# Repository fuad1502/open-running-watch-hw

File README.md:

# *open-running-watch* (Hardware Repository)

An Open Source GPS Running Watch. 🏃⌚

> Note: This is the hardware repository. The firmware repository isn't available yet.

## Motivation

Running is my hobby, and ask anyone who has taken their running hobby seriously and they'll tell you having a GPS running watch is a must. Throughout my time using one, I sometimes encounter issues and thought to myself, "Why does it happen?", "I wish I had access to the raw data", "Why is the latest model way more expensive for just an additional sensor or software feature?", "I wish I could tune my watch to the way I wanted it, for longer battery life or better user experience", etc.

My wishes can only be fulfilled if there is a GPS running watch out there that is open sourced. Free for everyone to add their own software features, experiment with different algorithms, different chips, and produce their own customized hardware version, designed to exactly what they want.

I know what you're thinking. Who in the world would want that? Firstly, they have to be a runner, secondly, they have to be either a hardware geek and / or a software geek. Well, I am both! So I want it! And that's a good enough reason for me to build this 😁

However, in truth, that's not actually my main motivation for initiating this project. **My main motivation is I wanted to try out [Zephyr Project](https://www.zephyrproject.org/) on a complex embedded system.**

## Main components

- Main controller (STM32L475RGT6)
- Display (Azumo 12616: Sharp LS018B7DH02 Memory in Pixel Display)
- GPS receiver (TESEO-LIV3F)
- BLE wireless network coprocessor (BLUENRG-232N)
- Barometric pressure sensor (ICP-10100)
- Accelerometer (LIS2DE12TR)
- PPG Sensor (SFH7072)
- NAND Flash Memory (W25N512GVEIG)
- Fuel gauge & charge controller
- Audio indicator
- 5 user input buttons
- Current sense amplifiers for power usage monitoring in the development phase

## PCB Stackup

I use [JLCPCB JLC04161H-7628](https://jlcpcb.com/impedance) 4 layer stackup with the following signal assignments:

```
=========================
= (F.Cu) SIGNAL         =
=========================
PREPREG
=========================
= (In1.Cu) GROUND PLANE =
=========================
CORE
=========================
= (In2.Cu) POWER PLANE  =
=========================
PREPREG
=========================
= (B.Cu) SIGNAL         =
=========================
```

## Fabrication Files

You can download the released fabrication files tarball in the [Release](https://github.com/fuad1502/open-running-watch-hw/releases) tab. It contains:
- Schematic PDF.
- Top, bottom, and power plane PCB drawing.
- Gerbers.
- Bill of Materials.

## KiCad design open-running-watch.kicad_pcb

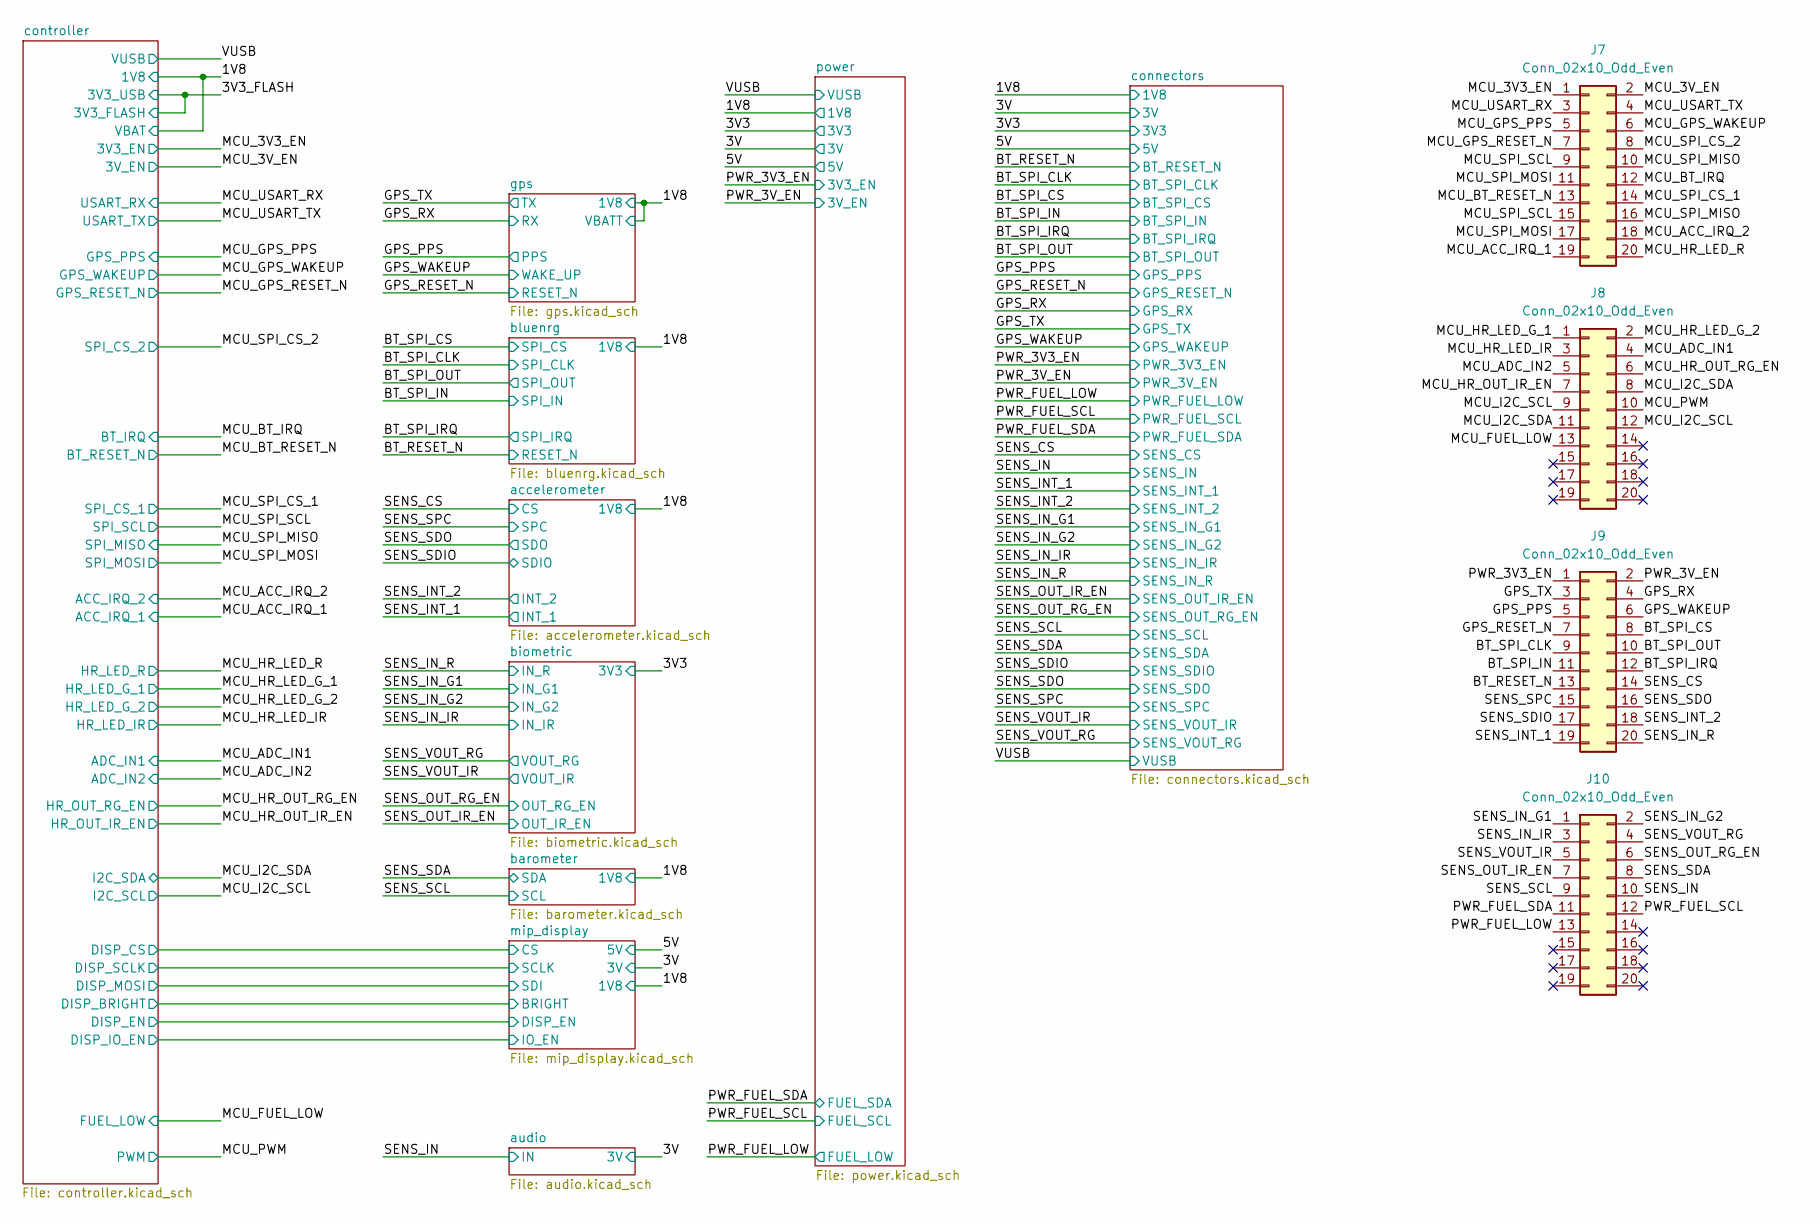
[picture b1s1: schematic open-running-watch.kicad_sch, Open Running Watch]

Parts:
J7, J8, J9, J10: Conn_02x10_Odd_Even; PinHeader_2x10_P2.54mm_Vertical_SMD

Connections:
/BT_RESET_N: J9.13; also elsewhere on the board
/BT_SPI_CLK: J9.9; also elsewhere on the board
/BT_SPI_CS: J9.8; also elsewhere on the board
/BT_SPI_IN: J9.11; also elsewhere on the board
/BT_SPI_IRQ: J9.12; also elsewhere on the board
/BT_SPI_OUT: J9.10; also elsewhere on the board
/GPS_PPS: J9.5; also elsewhere on the board
/GPS_RESET_N: J9.7; also elsewhere on the board
/GPS_RX: J9.4; also elsewhere on the board
/GPS_TX: J9.3; also elsewhere on the board
/GPS_WAKEUP: J9.6; also elsewhere on the board
/MCU_3V3_EN: J7.1
/MCU_3V_EN: J7.2
/MCU_ACC_IRQ_1: J7.19; also elsewhere on the board
/MCU_ACC_IRQ_2: J7.18; also elsewhere on the board
/MCU_ADC_IN1: J8.4; also elsewhere on the board
/MCU_ADC_IN2: J8.5; also elsewhere on the board
/MCU_BT_IRQ: J7.12; also elsewhere on the board
/MCU_BT_RESET_N: J7.13; also elsewhere on the board
/MCU_FUEL_LOW: J8.13
/MCU_GPS_PPS: J7.5
/MCU_GPS_RESET_N: J7.7; also elsewhere on the board
/MCU_GPS_WAKEUP: J7.6; also elsewhere on the board
/MCU_HR_LED_G_1: J8.1; also elsewhere on the board
/MCU_HR_LED_G_2: J8.2; also elsewhere on the board
/MCU_HR_LED_IR: J8.3; also elsewhere on the board
/MCU_HR_LED_R: J7.20; also elsewhere on the board
/MCU_HR_OUT_IR_EN: J8.6, J8.7; also elsewhere on the board
/MCU_I2C_SCL: J8.9, J8.12; also elsewhere on the board
/MCU_I2C_SDA: J8.8, J8.11; also elsewhere on the board
/MCU_PWM: J8.10; also elsewhere on the board
/MCU_SPI_CS_1: J7.14; also elsewhere on the board
/MCU_SPI_CS_2: J7.8; also elsewhere on the board
/MCU_SPI_MISO: J7.10, J7.16; also elsewhere on the board
/MCU_SPI_MOSI: J7.11, J7.17; also elsewhere on the board
/MCU_SPI_SCL: J7.9, J7.15; also elsewhere on the board
/MCU_USART_RX: J7.3; also elsewhere on the board
/MCU_USART_TX: J7.4; also elsewhere on the board
/PWR_3V3_EN: J9.1; also elsewhere on the board
/PWR_3V_EN: J9.2; also elsewhere on the board
/PWR_FUEL_LOW: J10.13; also elsewhere on the board
/PWR_FUEL_SCL: J10.12; also elsewhere on the board
/PWR_FUEL_SDA: J10.11; also elsewhere on the board
/SENS_CS: J9.14; also elsewhere on the board
/SENS_IN: J10.10; also elsewhere on the board
/SENS_INT_1: J9.19; also elsewhere on the board
/SENS_INT_2: J9.18; also elsewhere on the board
/SENS_IN_G1: J10.1; also elsewhere on the board
/SENS_IN_G2: J10.2; also elsewhere on the board
/SENS_IN_IR: J10.3; also elsewhere on the board
/SENS_IN_R: J9.20; also elsewhere on the board
/SENS_OUT_IR_EN: J10.7; also elsewhere on the board
/SENS_OUT_RG_EN: J10.6; also elsewhere on the board
/SENS_SCL: J10.9; also elsewhere on the board
/SENS_SDA: J10.8; also elsewhere on the board
/SENS_SDIO: J9.17; also elsewhere on the board
/SENS_SDO: J9.16; also elsewhere on the board
/SENS_SPC: J9.15; also elsewhere on the board
/SENS_VOUT_IR: J10.5; also elsewhere on the board
/SENS_VOUT_RG: J10.4; also elsewhere on the board

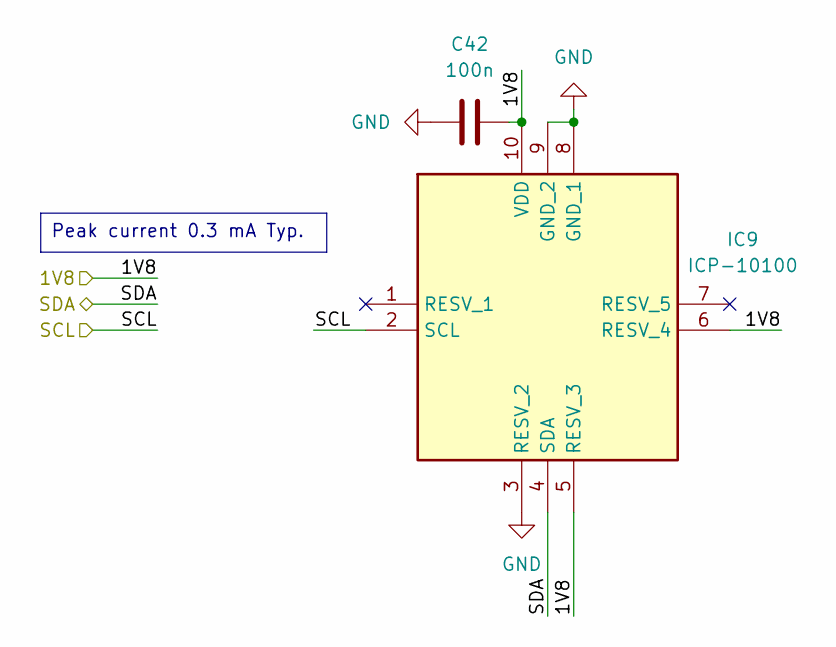
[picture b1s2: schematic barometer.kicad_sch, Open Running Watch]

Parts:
C42: 100n; C_0402_1005Metric; Manufacturer_Part_Number GRM155R71A104MA01D
IC9: ICP-10100; ICP10100; Mouser Part Number 410-ICP-10100

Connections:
/1V8: C42.2, IC9.5 (RESV_3), IC9.6 (RESV_4), IC9.10 (VDD); also elsewhere on the board
/SENS_SCL: IC9.2 (SCL); also elsewhere on the board
/SENS_SDA: IC9.4 (SDA); also elsewhere on the board
GND: C42.1, IC9.3 (RESV_2), IC9.8 (GND_1), IC9.9 (GND_2); also elsewhere on the board

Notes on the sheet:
Peak current 0.3 mA Typ.

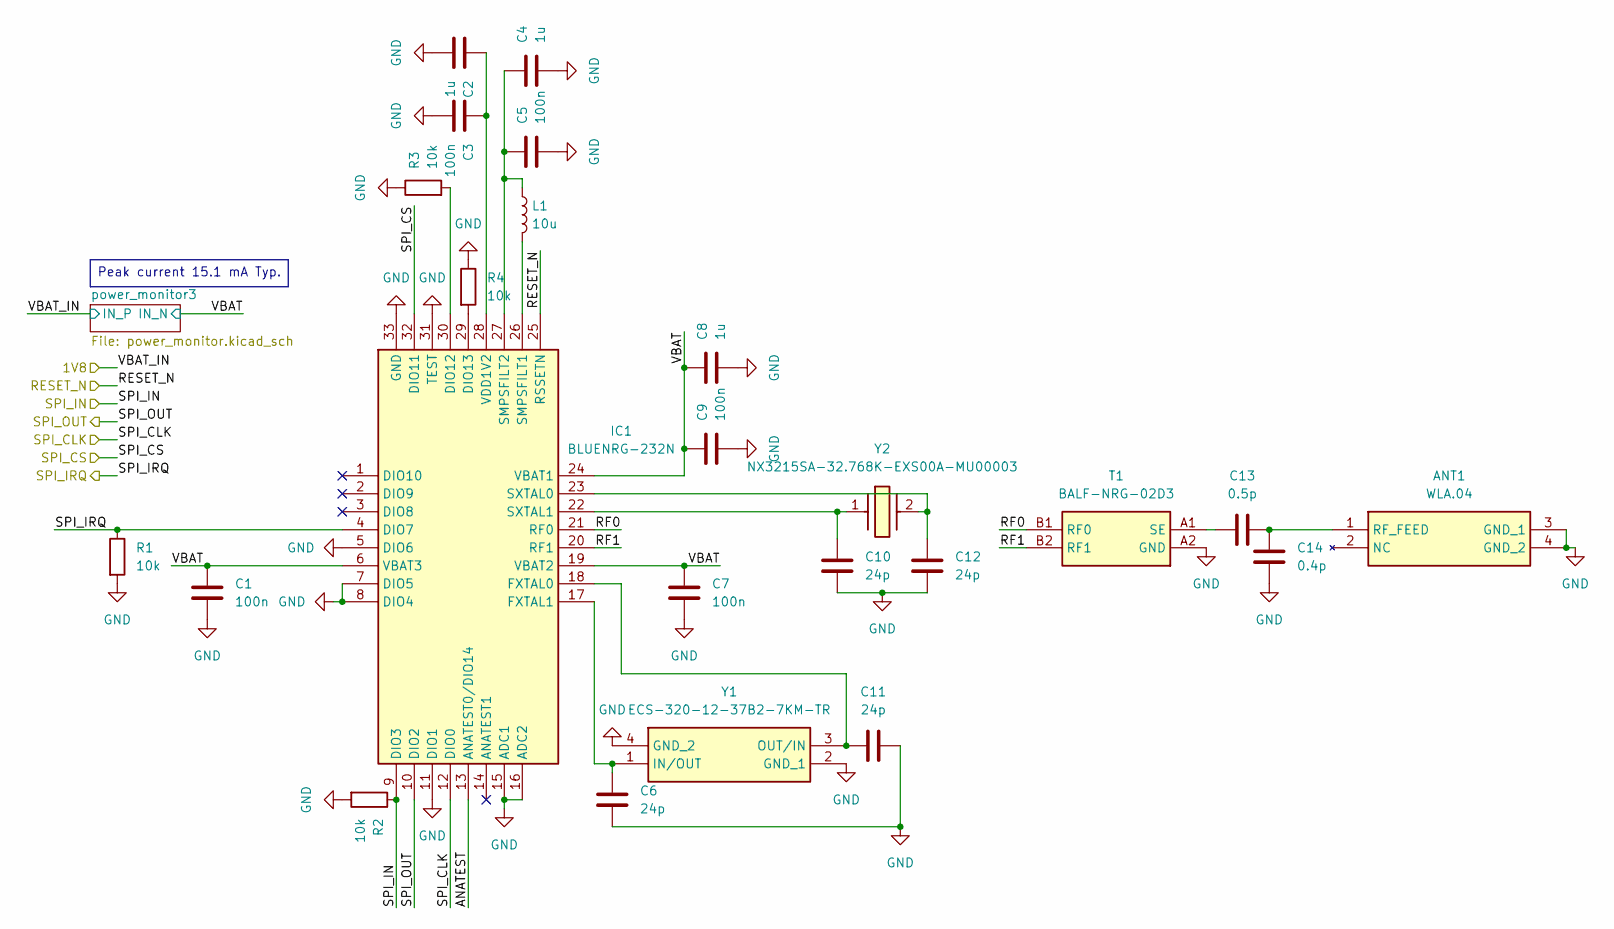
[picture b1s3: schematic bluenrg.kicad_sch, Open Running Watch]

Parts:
ANT1: WLA.04; WLA04; Mouser Part Number 960-WLA.04
C1, C3, C5, C7, C9: 100n; C_0402_1005Metric; Manufacturer_Part_Number GRM155R71A104MA01D
C2, C4, C8: 1u; C_0603_1608Metric; Manufacturer_Part_Number C0603C105K4RACTU
C6, C10, C11, C12: 24p; C_0402_1005Metric; Manufacturer_Part_Number GRT1555C1H240FA02D
C13: 0.5p; C_0402_1005Metric; Manufacturer_Part_Number GCQ1555C1HR50CB01D
C14: 0.4p; C_0402_1005Metric; Manufacturer_Part_Number GCQ1555C1HR40CB01D
IC1: BLUENRG-232N; QFN50P500X500X100-33N-D; Mouser Part Number 511-BLUENRG-232N
L1: 10u; L_0805_2012Metric; Manufacturer_Part_Number MLZ2012N100LT000
R1, R2, R3, R4: 10k; R_0402_1005Metric; Manufacturer_Part_Number RC0402JR-0710KP
T1: BALF-NRG-02D3; BALFNRG02D3; Mouser Part Number 511-BALF-NRG-02D3
Y1: ECS-320-12-37B2-7KM-TR; ECS3201237B27KMTR; Mouser Part Number 520-320-12-37B27KMTR
Y2: NX3215SA-32.768K-EXS00A-MU00003; NX3215SA32768KEXS00AMU00003; Mouser Part Number 344-NX3215SA32.768K3

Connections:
/BT_RESET_N: IC1.25 (RSSETN); also elsewhere on the board
/BT_SPI_CLK: IC1.12 (DIO0); also elsewhere on the board
/BT_SPI_CS: IC1.32 (DIO11); also elsewhere on the board
/BT_SPI_IN: IC1.9 (DIO3), R2.1; also elsewhere on the board
/BT_SPI_IRQ: IC1.4 (DIO7), R1.1; also elsewhere on the board
/BT_SPI_OUT: IC1.10 (DIO2); also elsewhere on the board
/bluenrg/ANATEST: IC1.13 (ANATEST0/DIO14)
/bluenrg/RF0: IC1.21 (RF0), T1.B1 (RF0)
/bluenrg/RF1: IC1.20 (RF1), T1.B2 (RF1)
/bluenrg/VBAT: C1.1, C7.1, C8.1, C9.1, IC1.6 (VBAT3), IC1.19 (VBAT2), IC1.24 (VBAT1); also elsewhere on the board
GND: ANT1.3 (GND_1), ANT1.4 (GND_2), C1.2, C2.2, C3.2, C4.2, C5.2, C6.2, C7.2, C8.2, C9.2, C10.2, C11.2, C12.2, C14.2, IC1.5 (DIO6), IC1.7 (DIO5), IC1.8 (DIO4), IC1.11 (DIO1), IC1.15 (ADC1), IC1.16 (ADC2), IC1.31 (TEST), IC1.33 (GND), R1.2, R2.2, R3.1, R4.1, T1.A2 (GND), Y1.2 (GND_1), Y1.4 (GND_2); also elsewhere on the board
unnamed: ANT1.1 (RF_FEED), C13.2, C14.1
unnamed: IC1.30 (DIO12), R3.2
unnamed: IC1.29 (DIO13), R4.2
unnamed: C11.1, IC1.18 (FXTAL0), Y1.3 (OUT/IN)
unnamed: C6.1, IC1.17 (FXTAL1), Y1.1 (IN/OUT)
unnamed: IC1.26 (SMPSFILT1), L1.2
unnamed: C4.1, C5.1, IC1.27 (SMPSFILT2), L1.1
unnamed: C12.1, IC1.23 (SXTAL0), Y2.2
unnamed: C10.1, IC1.22 (SXTAL1), Y2.1
unnamed: C2.1, C3.1, IC1.28 (VDD1V2)
unnamed: C13.1, T1.A1 (SE)

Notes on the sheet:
Peak current 15.1 mA Typ.

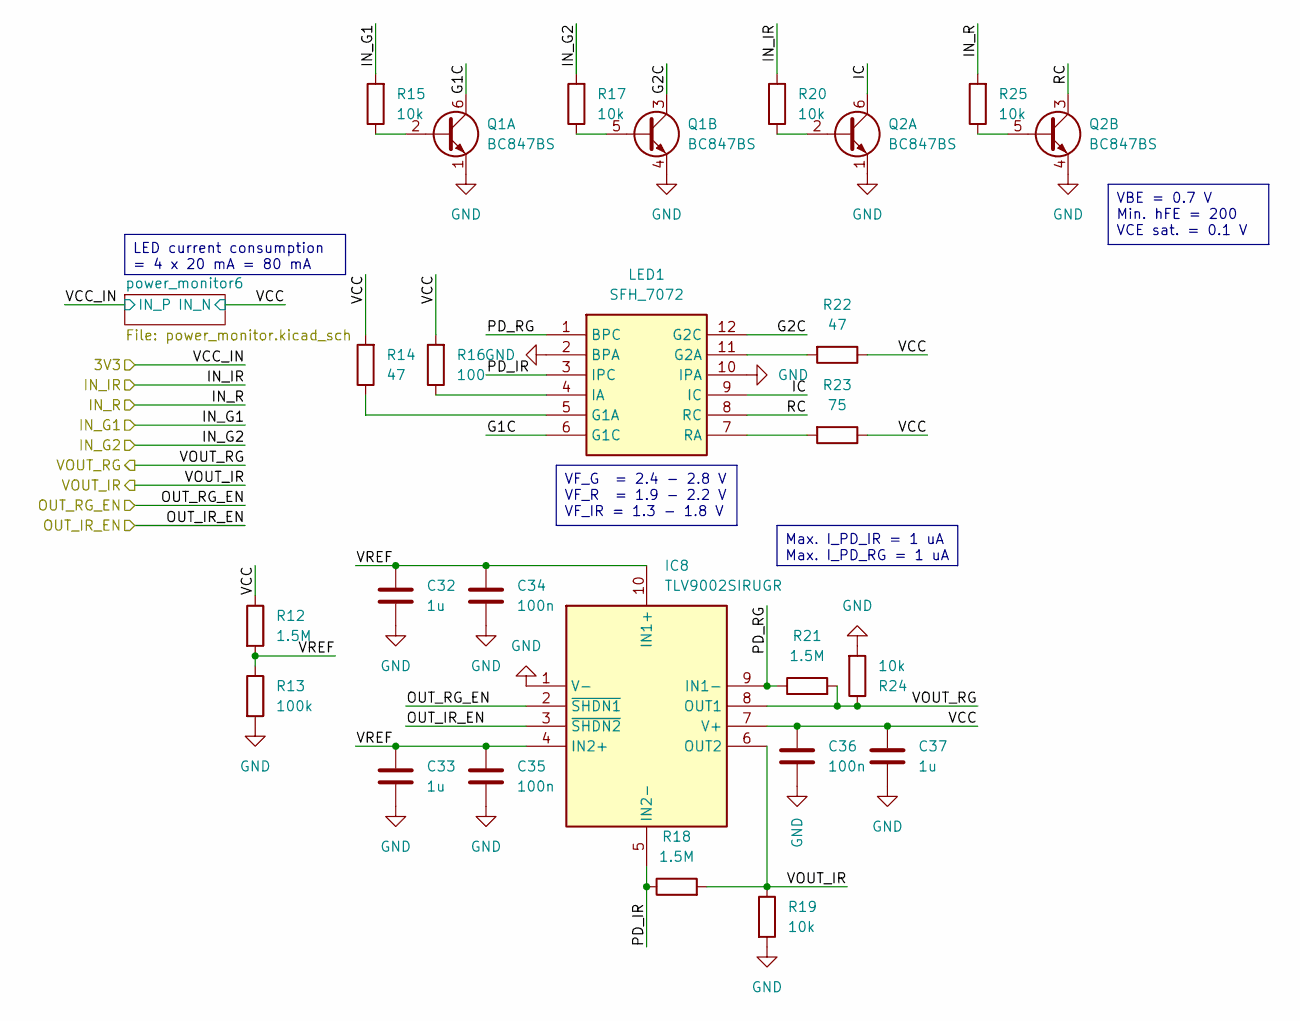
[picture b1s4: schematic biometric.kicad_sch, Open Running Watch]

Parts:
C32, C33, C37: 1u; C_0603_1608Metric; Manufacturer_Part_Number C0603C105K4RACTU
C34, C35, C36: 100n; C_0402_1005Metric; Manufacturer_Part_Number GRM155R71A104MA01D
IC8: TLV9002SIRUGR; QFN50P150X200X40-10N; Mouser Part Number 595-TLV9002SIRUGR
LED1: SFH_7072; SFH7072; Mouser Part Number 720-SFH7072
Q1, Q2: BC847BS; SOT-363_SC-70-6; Manufacturer_Part_Number BC847BS,135
R12, R18, R21: 1.5M; R_0402_1005Metric; Manufacturer_Part_Number AC0402FR-071M5L
R13: 100k; R_0402_1005Metric; Manufacturer_Part_Number RC0402JR-7D100KL
R14, R22: 47; R_0402_1005Metric; Manufacturer_Part_Number RC0402JR-0747RL
R15, R17, R19, R20, R24, R25: 10k; R_0402_1005Metric; Manufacturer_Part_Number RC0402JR-0710KP
R16: 100; R_0402_1005Metric; Manufacturer_Part_Number AC0402FR-13100RL
R23: 75; R_0402_1005Metric; Manufacturer_Part_Number RC0402JR-0775RL

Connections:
/SENS_IN_G1: R15.2; also elsewhere on the board
/SENS_IN_G2: R17.2; also elsewhere on the board
/SENS_IN_IR: R20.2; also elsewhere on the board
/SENS_IN_R: R25.2; also elsewhere on the board
/SENS_OUT_IR_EN: IC8.3 (~SHDN2); also elsewhere on the board
/SENS_OUT_RG_EN: IC8.2 (~SHDN1); also elsewhere on the board
/SENS_VOUT_IR: IC8.6 (OUT2), R18.2, R19.1; also elsewhere on the board
/SENS_VOUT_RG: IC8.8 (OUT1), R21.2, R24.1; also elsewhere on the board
/biometric/G1C: LED1.6 (G1C), Q1.6 (C1)
/biometric/G2C: LED1.12 (G2C), Q1.3 (C2)
/biometric/IC: LED1.9 (IC), Q2.6 (C1)
/biometric/PD_IR: IC8.5 (IN2-), LED1.3 (IPC), R18.1
/biometric/PD_RG: IC8.9 (IN1-), LED1.1 (BPC), R21.1
/biometric/RC: LED1.8 (RC), Q2.3 (C2)
/biometric/VCC: C36.1, C37.1, IC8.7 (V+), R12.1, R14.2, R16.2, R22.1, R23.1; also elsewhere on the board
/biometric/VREF: C32.1, C33.1, C34.1, C35.1, IC8.4 (IN2+), IC8.10 (IN1+), R12.2, R13.1
GND: C32.2, C33.2, C34.2, C35.2, C36.2, C37.2, IC8.1 (V-), LED1.2 (BPA), LED1.10 (IPA), Q1.1 (E1), Q1.4 (E2), Q2.1 (E1), Q2.4 (E2), R13.2, R19.2, R24.2; also elsewhere on the board
unnamed: LED1.5 (G1A), R14.1
unnamed: LED1.11 (G2A), R22.2
unnamed: LED1.4 (IA), R16.1
unnamed: LED1.7 (RA), R23.2
unnamed: Q1.2 (B1), R15.1
unnamed: Q1.5 (B2), R17.1
unnamed: Q2.2 (B1), R20.1
unnamed: Q2.5 (B2), R25.1

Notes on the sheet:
Max. I_PD_IR = 1 uA Max. I_PD_RG = 1 uA
LED current consumption = 4 x 20 mA = 80 mA
VF_G = 2.4 - 2.8 V VF_R = 1.9 - 2.2 V VF_IR = 1.3 - 1.8 V
VBE = 0.7 V Min. hFE = 200 VCE sat. = 0.1 V

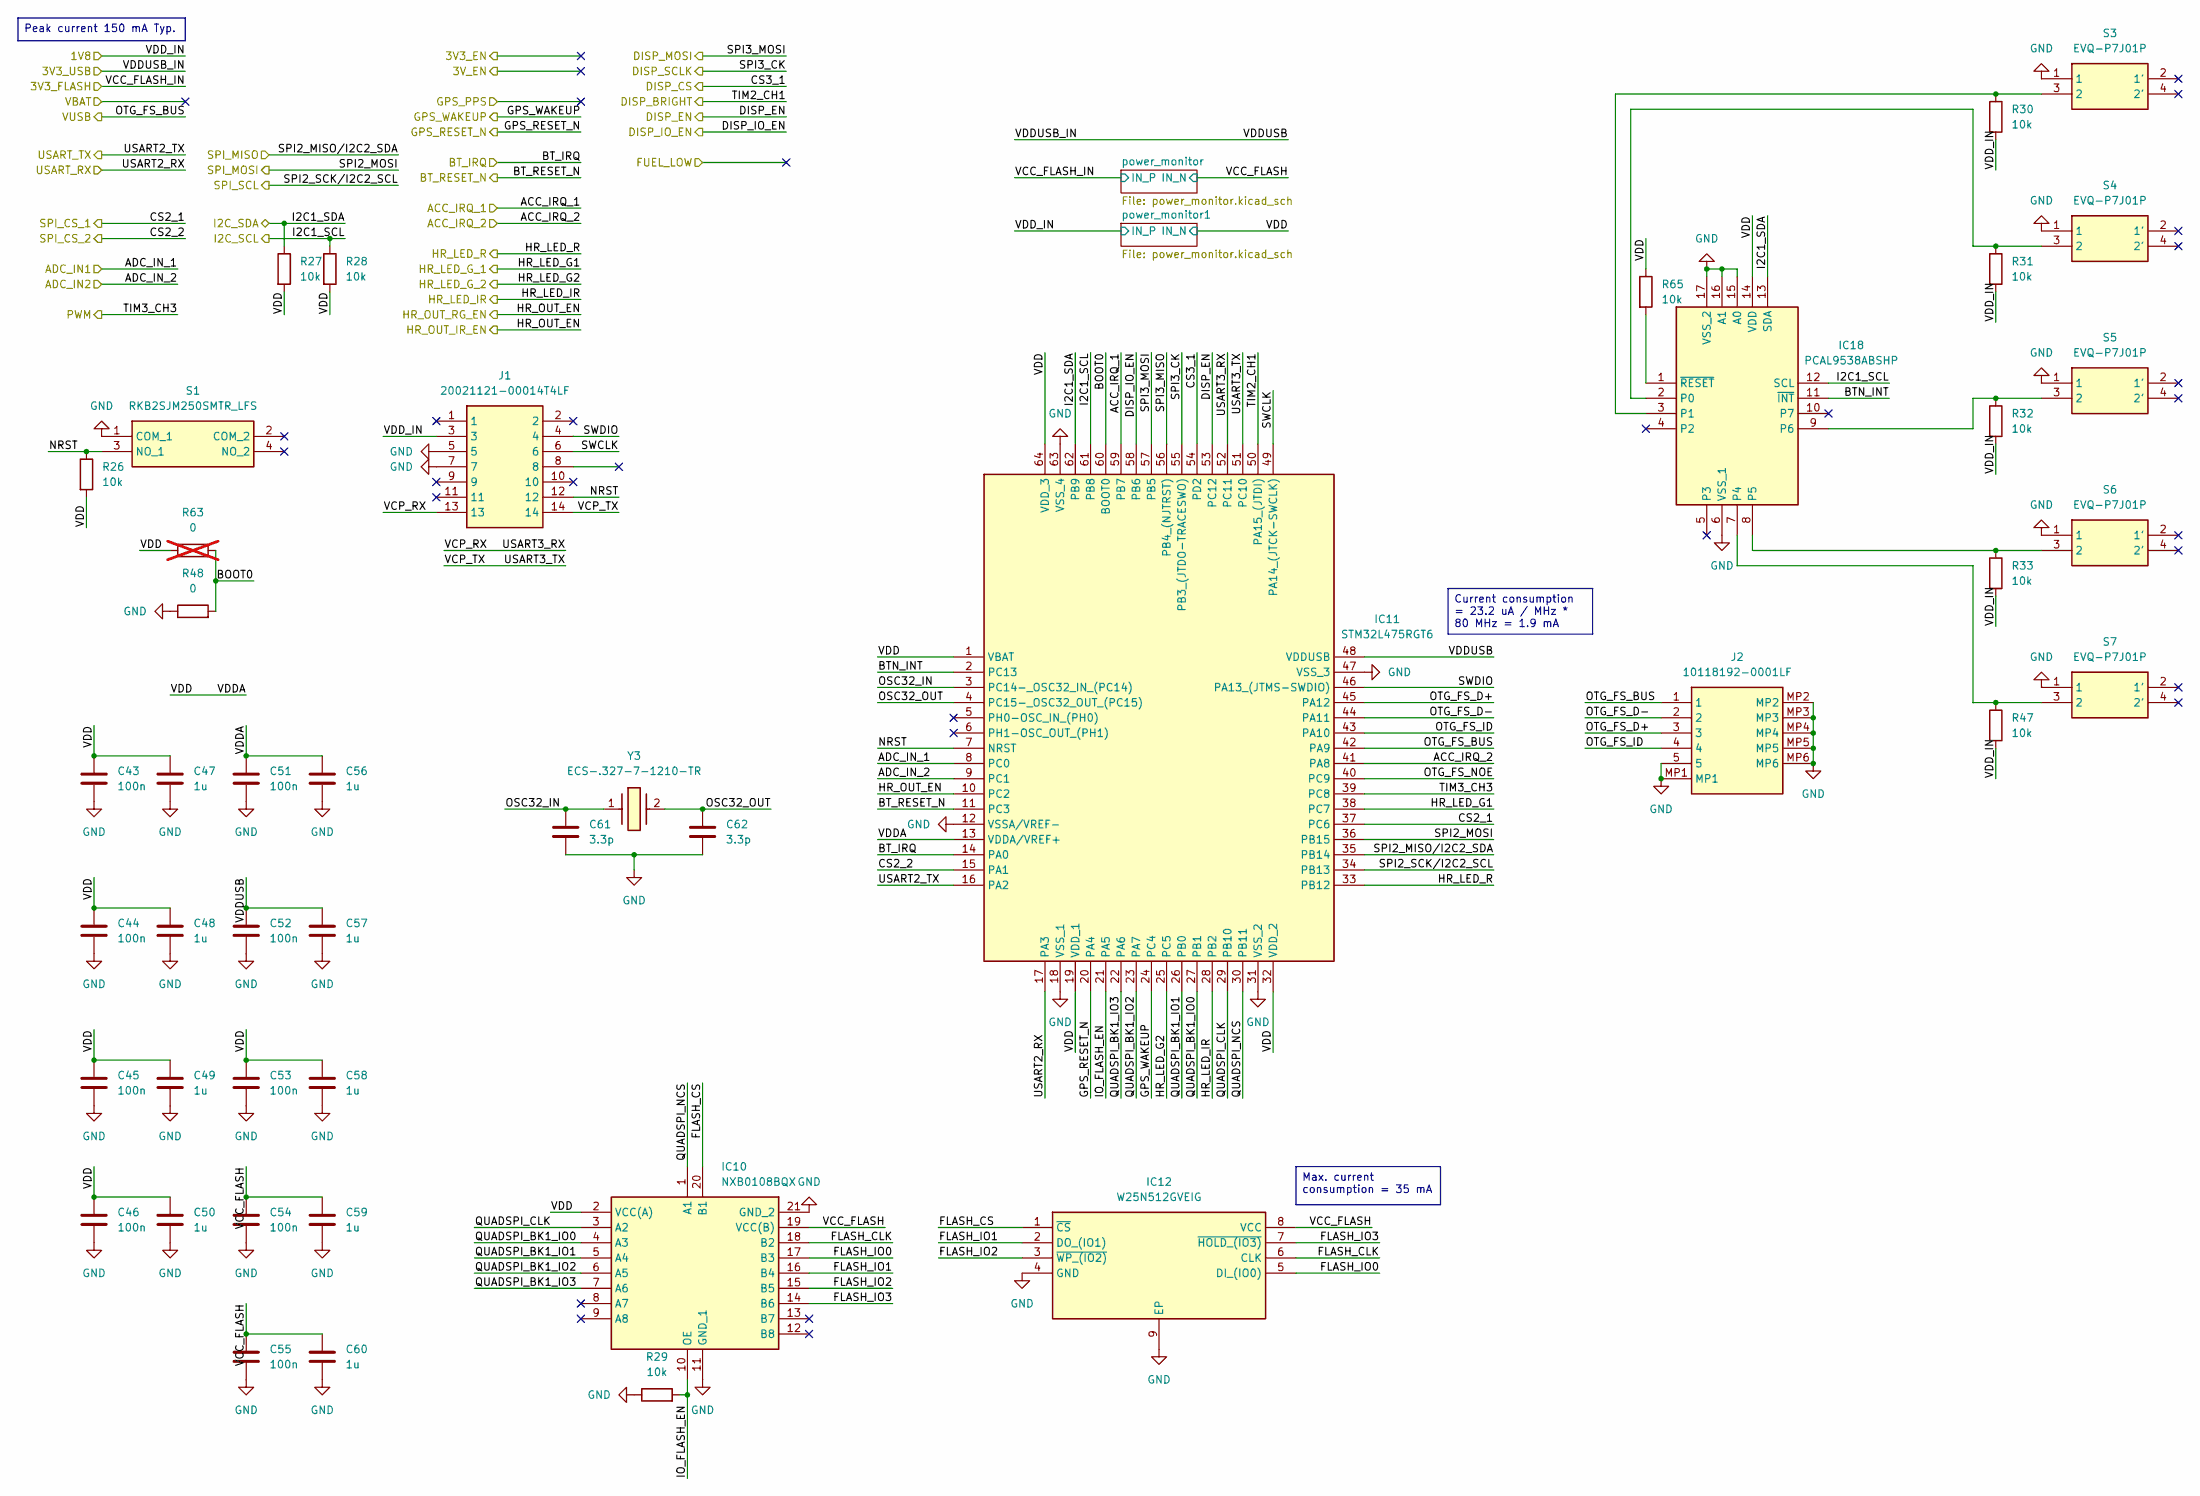
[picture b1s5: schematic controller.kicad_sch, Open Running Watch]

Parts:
C43, C44, C45, C46, C51, C52, C53, C54, C55: 100n; C_0402_1005Metric; Manufacturer_Part_Number GRM155R71A104MA01D
C47, C48, C49, C50, C56, C57, C58, C59, C60: 1u; C_0603_1608Metric; Manufacturer_Part_Number C0603C105K4RACTU
C61, C62: 3.3p; C_0402_1005Metric; Manufacturer_Part_Number GRM1555C1E3R3WA01D
IC10: NXB0108BQX; Mouser Part Number 771-NXB0108BQX
IC11: STM32L475RGT6; QFP50P1200X1200X160-64N; Mouser Part Number 511-STM32L475RGT6
IC12: W25N512GVEIG; SON127P800X600X80-9N-D; Mouser Part Number 454-W25N512GVEIG
IC18: PCAL9538ABSHP; QFN50P300X300X100-17N-D; Mouser Part Number 771-PCAL9538ABSHP
J1: 20021121-00014T4LF; 2002112100014T4LF; Mouser Part Number 649-221121-00014T4LF
J2: 10118192-0001LF; 101181920001LF; Manufacturer_Part_Number 10118192-0001LF
R26, R27, R28, R29, R30, R31, R32, R33, R47, R65: 10k; R_0402_1005Metric; Manufacturer_Part_Number RC0402JR-0710KP
R48: 0; R_0402_1005Metric_Pad0.72x0.64mm_HandSolder; Manufacturer_Part_Number AC0402JR-7D0RL
R63: 0; R_0402_1005Metric_Pad0.72x0.64mm_HandSolder; Manufacturer_Part_Number AC0402JR-7D0RL; not fitted
S1: RKB2SJM250SMTR_LFS; RKB2SJM250SMTRLFS; Mouser Part Number 611-RKB2SJM250SMTRLF
S3, S4, S5, S6, S7: EVQ-P7J01P; EVQP7J01P; Mouser Part Number 667-EVQP7J01P
Y3: ECS-.327-7-1210-TR; ECS32791210TR; Mouser Part Number 520-.327-7-1210T

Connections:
/1V8: J1.3, R30.2, R31.2, R32.2, R33.2, R47.2; also elsewhere on the board
/3V3_FLASH: C52.1, C57.1, IC11.48 (VDDUSB); also elsewhere on the board
/MCU_ACC_IRQ_1: IC11.59 (PB7); also elsewhere on the board
/MCU_ACC_IRQ_2: IC11.41 (PA8); also elsewhere on the board
/MCU_ADC_IN1: IC11.8 (PC0); also elsewhere on the board
/MCU_ADC_IN2: IC11.9 (PC1); also elsewhere on the board
/MCU_BT_IRQ: IC11.14 (PA0); also elsewhere on the board
/MCU_BT_RESET_N: IC11.11 (PC3); also elsewhere on the board
/MCU_GPS_RESET_N: IC11.20 (PA4); also elsewhere on the board
/MCU_GPS_WAKEUP: IC11.24 (PC4); also elsewhere on the board
/MCU_HR_LED_G_1: IC11.38 (PC7); also elsewhere on the board
/MCU_HR_LED_G_2: IC11.25 (PC5); also elsewhere on the board
/MCU_HR_LED_IR: IC11.28 (PB2); also elsewhere on the board
/MCU_HR_LED_R: IC11.33 (PB12); also elsewhere on the board
/MCU_HR_OUT_IR_EN: IC11.10 (PC2); also elsewhere on the board
/MCU_I2C_SCL: IC11.61 (PB8), IC18.12 (SCL), R28.1; also elsewhere on the board
/MCU_I2C_SDA: IC11.62 (PB9), IC18.13 (SDA), R27.1; also elsewhere on the board
/MCU_PWM: IC11.39 (PC8); also elsewhere on the board
/MCU_SPI_CS_1: IC11.37 (PC6); also elsewhere on the board
/MCU_SPI_CS_2: IC11.15 (PA1); also elsewhere on the board
/MCU_SPI_MISO: IC11.35 (PB14); also elsewhere on the board
/MCU_SPI_MOSI: IC11.36 (PB15); also elsewhere on the board
/MCU_SPI_SCL: IC11.34 (PB13); also elsewhere on the board
/MCU_USART_RX: IC11.17 (PA3); also elsewhere on the board
/MCU_USART_TX: IC11.16 (PA2); also elsewhere on the board
/VUSB: IC11.42 (PA9), J2.1; also elsewhere on the board
/controller/BOOT0: IC11.60 (BOOT0), R48.2, R63.2
/controller/BTN_INT: IC11.2 (PC13), IC18.11 (~INT)
/controller/CS3_1: IC11.54 (PD2); also elsewhere on the board
/controller/DISP_EN: IC11.53 (PC12); also elsewhere on the board
/controller/DISP_IO_EN: IC11.58 (PB6); also elsewhere on the board
/controller/FLASH_CLK: IC10.18 (B2), IC12.6 (CLK)
/controller/FLASH_CS: IC10.20 (B1), IC12.1 (~CS)
/controller/FLASH_IO0: IC10.17 (B3), IC12.5 (DI_(IO0))
/controller/FLASH_IO1: IC10.16 (B4), IC12.2 (DO_(IO1))
/controller/FLASH_IO2: IC10.15 (B5), IC12.3 (~WP_(IO2))
/controller/FLASH_IO3: IC10.14 (B6), IC12.7 (~HOLD_(IO3))
/controller/IO_FLASH_EN: IC10.10 (OE), IC11.21 (PA5), R29.2
/controller/NRST: IC11.7 (NRST), J1.12, R26.1, S1.3 (NO_1)
/controller/OSC32_IN: C61.1, IC11.3 (PC14-_OSC32_IN_(PC14)), Y3.1
/controller/OSC32_OUT: C62.1, IC11.4 (PC15-_OSC32_OUT_(PC15)), Y3.2
/controller/OTG_FS_D+: IC11.45 (PA12), J2.3
/controller/OTG_FS_D-: IC11.44 (PA11), J2.2
/controller/OTG_FS_ID: IC11.43 (PA10), J2.4
/controller/OTG_FS_NOE: IC11.40 (PC9)
/controller/QUADSPI_BK1_IO0: IC10.4 (A3), IC11.27 (PB1)
/controller/QUADSPI_BK1_IO1: IC10.5 (A4), IC11.26 (PB0)
/controller/QUADSPI_BK1_IO2: IC10.6 (A5), IC11.23 (PA7)
/controller/QUADSPI_BK1_IO3: IC10.7 (A6), IC11.22 (PA6)
/controller/QUADSPI_CLK: IC10.3 (A2), IC11.29 (PB10)
/controller/QUADSPI_NCS: IC10.1 (A1), IC11.30 (PB11)
/controller/SPI3_CK: IC11.55 (PB3_(JTDO-TRACESWO)); also elsewhere on the board
/controller/SPI3_MISO: IC11.56 (PB4_(NJTRST))
/controller/SPI3_MOSI: IC11.57 (PB5); also elsewhere on the board
/controller/SWCLK: IC11.49 (PA14_(JTCK-SWCLK)), J1.6
/controller/SWDIO: IC11.46 (PA13_(JTMS-SWDIO)), J1.4
/controller/TIM2_CH1: IC11.50 (PA15_(JTDI)); also elsewhere on the board
/controller/USART3_RX: IC11.52 (PC11), J1.13
/controller/USART3_TX: IC11.51 (PC10), J1.14
/controller/VCC_FLASH: C54.1, C55.1, C59.1, C60.1, IC10.19 (VCC(B)), IC12.8 (VCC); also elsewhere on the board
/controller/VDD: C43.1, C44.1, C45.1, C46.1, C47.1, C48.1, C49.1, C50.1, C51.1, C53.1, C56.1, C58.1, IC10.2 (VCC(A)), IC11.1 (VBAT), IC11.13 (VDDA/VREF+), IC11.19 (VDD_1), IC11.32 (VDD_2), IC11.64 (VDD_3), IC18.14 (VDD), R26.2, R27.2, R28.2, R63.1, R65.1; also elsewhere on the board
GND: C43.2, C44.2, C45.2, C46.2, C47.2, C48.2, C49.2, C50.2, C51.2, C52.2, C53.2, C54.2, C55.2, C56.2, C57.2, C58.2, C59.2, C60.2, C61.2, C62.2, IC10.11 (GND_1), IC10.21 (GND_2), IC11.12 (VSSA/VREF-), IC11.18 (VSS_1), IC11.31 (VSS_2), IC11.47 (VSS_3), IC11.63 (VSS_4), IC12.4 (GND), IC12.9 (EP), IC18.6 (VSS_1), IC18.15 (A0), IC18.16 (A1), IC18.17 (VSS_2), J1.5, J1.7, J2.5, J2.MP1, J2.MP2, J2.MP3, J2.MP4, J2.MP5, J2.MP6, R29.1, R48.1, S1.1 (COM_1), S3.1, S4.1, S5.1, S6.1, S7.1; also elsewhere on the board
unnamed: IC18.2 (P0), R31.1, S4.3 (2)
unnamed: IC18.3 (P1), R30.1, S3.3 (2)
unnamed: IC18.7 (P4), R47.1, S7.3 (2)
unnamed: IC18.8 (P5), R33.1, S6.3 (2)
unnamed: IC18.9 (P6), R32.1, S5.3 (2)
unnamed: IC18.1 (~RESET), R65.2

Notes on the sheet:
Peak current 150 mA Typ.
Current consumption = 23.2 uA / MHz * 80 MHz = 1.9 mA
Max. current consumption = 35 mA

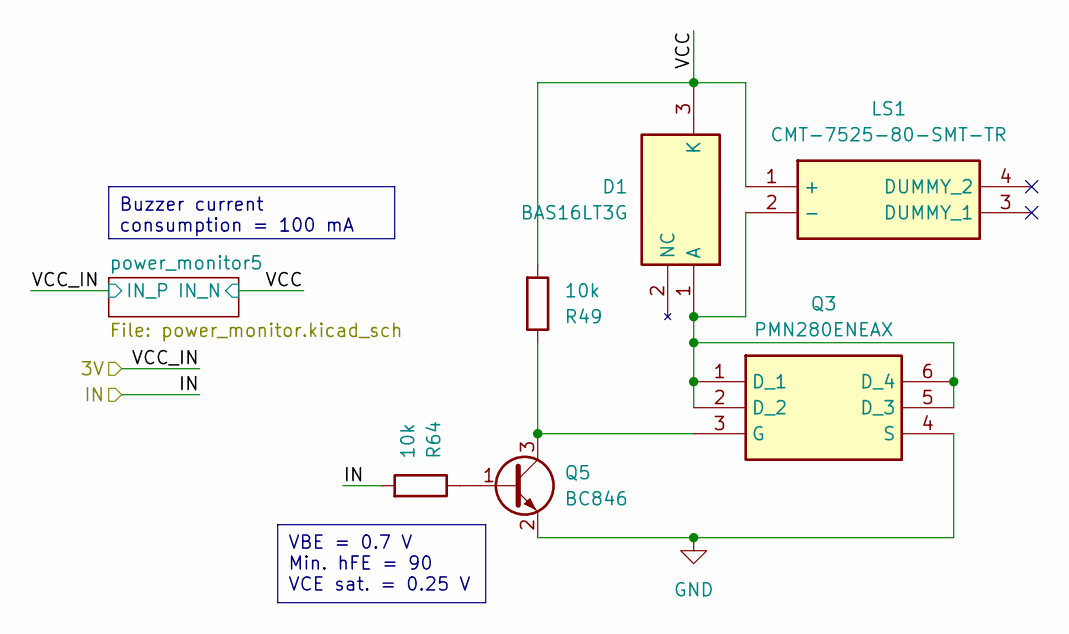
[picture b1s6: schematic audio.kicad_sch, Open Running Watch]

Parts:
D1: BAS16LT3G; SOT96P237X111-3N; Mouser Part Number 863-BAS16LT3G
LS1: CMT-7525-80-SMT-TR; CMT752580SMTTR; Mouser Part Number 490-CMT-7525-80SMTTR
Q3: PMN280ENEAX; Mouser Part Number 771-PMN280ENEAX
Q5: BC846; SOT-23; Manufacturer_Part_Number BC847BLT1G
R49, R64: 10k; R_0402_1005Metric; Manufacturer_Part_Number RC0402JR-0710KP

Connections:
/SENS_IN: R64.2; also elsewhere on the board
/audio/VCC: D1.3 (K), LS1.1 (+), R49.2; also elsewhere on the board
GND: Q3.4 (S), Q5.2 (E); also elsewhere on the board
unnamed: D1.1 (A), LS1.2 (-), Q3.1 (D_1), Q3.2 (D_2), Q3.5 (D_3), Q3.6 (D_4)
unnamed: Q3.3 (G), Q5.3 (C), R49.1
unnamed: Q5.1 (B), R64.1

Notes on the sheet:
Buzzer current consumption = 100 mA
VBE = 0.7 V Min. hFE = 90 VCE sat. = 0.25 V

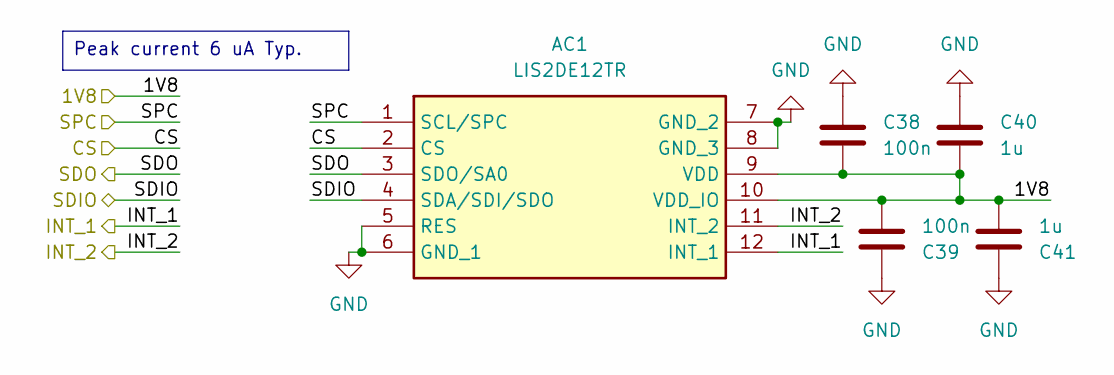
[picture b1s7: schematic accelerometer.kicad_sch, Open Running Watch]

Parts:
AC1: LIS2DE12TR; Mouser Part Number 511-LIS2DE12TR
C38, C39: 100n; C_0402_1005Metric; Manufacturer_Part_Number GRM155R71A104MA01D
C40, C41: 1u; C_0603_1608Metric; Manufacturer_Part_Number C0603C105K4RACTU

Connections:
/1V8: AC1.9 (VDD), AC1.10 (VDD_IO), C38.2, C39.2, C40.2, C41.2; also elsewhere on the board
/SENS_CS: AC1.2 (CS); also elsewhere on the board
/SENS_INT_1: AC1.12 (INT_1); also elsewhere on the board
/SENS_INT_2: AC1.11 (INT_2); also elsewhere on the board
/SENS_SDIO: AC1.4 (SDA/SDI/SDO); also elsewhere on the board
/SENS_SDO: AC1.3 (SDO/SA0); also elsewhere on the board
/SENS_SPC: AC1.1 (SCL/SPC); also elsewhere on the board
GND: AC1.5 (RES), AC1.6 (GND_1), AC1.7 (GND_2), AC1.8 (GND_3), C38.1, C39.1, C40.1, C41.1; also elsewhere on the board

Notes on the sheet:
Peak current 6 uA Typ.
